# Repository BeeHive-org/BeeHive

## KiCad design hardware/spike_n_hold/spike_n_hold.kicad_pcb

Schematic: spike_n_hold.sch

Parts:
C1, C2: 680pF; C_Disc_D5.1mm_W3.2mm_P5.00mm
C3, C4, C7, C8: 10nF; C_Disc_D5.1mm_W3.2mm_P5.00mm
C5, C6: 10µF; C_Disc_D5.1mm_W3.2mm_P5.00mm
C15: 22µF; CP_Radial_D5.0mm_P2.00mm
D1, D2, D3, D4, D5, D6: 1N4005; D_DO-41_SOD81_P10.16mm_Horizontal
D7, D8: 1N47xxA; D_DO-41_SOD81_P10.16mm_Horizontal
D17: 1N5822; D_DO-201AD_P15.24mm_Horizontal
H1, H2, H3, H4: MountingHole; MountingHole_3.2mm_M3
J1: Conn_01x04_Female; JST_XH_B4B-XH-A_1x04_P2.50mm_Vertical
J3: to_solenoid_2; PinHeader_1x02_P2.54mm_Vertical
J4: to_solenoid_1; PinHeader_1x02_P2.54mm_Vertical
J5, J6, J7: Conn_01x02; JST_XH_B2B-XH-A_1x02_P2.50mm_Vertical
L1: 33µH; L_Radial_D10.0mm_P5.00mm_Neosid_SD12_style3
Q1, Q2: MJH11021G; TO-247-3_Vertical
Q3, Q4, Q5, Q6: MPSA42; TO-92L_Inline_Wide; MPN MPSA42; Digi-Key_PN MPSA42FS-ND
Q7, Q8: MJH11022G; TO-247-3_Vertical
Q9: IRFZ24NPBF; TO-220-3_Vertical
R1, R2, R9, R10: 10k; R_Axial_DIN0411_L9.9mm_D3.6mm_P12.70mm_Horizontal
R3, R4: 4.7k; R_Axial_DIN0411_L9.9mm_D3.6mm_P12.70mm_Horizontal
R5, R6, R7, R8, R11, R12, R15, R16, R17: 330; R_Axial_DIN0411_L9.9mm_D3.6mm_P12.70mm_Horizontal
R13, R14: 2k; R_Axial_DIN0411_L9.9mm_D3.6mm_P12.70mm_Horizontal
R18: 1k; R_Axial_DIN0411_L9.9mm_D3.6mm_P12.70mm_Horizontal
U1, U2, U3: LM555xM; DIP-8_W7.62mm_LongPads

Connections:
+12V: D1.2 (A), D2.2 (A), J5.1, J6.1, L1.1, R9.2, R10.2, R13.2, R14.2, R15.1, U1.4 (R), U1.8 (VCC), U2.4 (R), U2.8 (VCC), U3.4 (R), U3.8 (VCC)
+24V: C15.1, D17.1 (K), J7.1, Q1.3 (E), Q2.3 (E), R1.1, R2.1
GND: C3.1, C4.1, C5.2, C6.2, C7.1, C8.1, C15.2, D3.2 (A), D4.2 (A), J1.4, J5.2, J6.2, J7.2, Q3.1 (E), Q4.1 (E), Q5.1 (E), Q6.1 (E), Q7.3 (E), Q8.3 (E), Q9.3 (S), R18.2, U1.1 (GND), U2.1 (GND), U3.1 (GND)
unnamed: C1.1, R5.2
unnamed: C2.1, R6.2
unnamed: C3.2, U1.5 (CV)
unnamed: C4.2, U2.5 (CV)
unnamed: C5.1, R13.1, U1.6 (THR), U1.7 (DIS)
unnamed: C6.1, R14.1, U2.6 (THR), U2.7 (DIS)
unnamed: C7.2, R16.1, U3.2 (TR), U3.6 (THR)
unnamed: C8.2, U3.5 (CV)
unnamed: D1.1 (K), D5.1 (K), J3.1, Q1.2 (C)
unnamed: D2.1 (K), D6.1 (K), J4.1, Q2.2 (C)
unnamed: D3.1 (K), Q3.2 (B), R5.1
unnamed: D4.1 (K), Q4.2 (B), R6.1
unnamed: D5.2 (A), D7.2 (A)
unnamed: D6.2 (A), D8.2 (A)
unnamed: D7.1 (K), J3.2, Q7.2 (C)
unnamed: D8.1 (K), J4.2, Q8.2 (C)
unnamed: D17.2 (A), L1.2, Q9.2 (D)
unnamed: Q1.1 (B), R3.2
unnamed: Q2.1 (B), R4.2
unnamed: Q3.3 (C), R9.1, U1.2 (TR)
unnamed: Q4.3 (C), R10.1, U2.2 (TR)
unnamed: Q5.2 (B), R7.1
unnamed: Q5.3 (C), R1.2, R3.1
unnamed: Q6.2 (B), R8.1
unnamed: Q6.3 (C), R2.2, R4.1
unnamed: Q7.1 (B), R11.1
unnamed: Q8.1 (B), R12.1
unnamed: Q9.1 (G), R17.2, R18.1
unnamed: R15.2, R16.2, U3.7 (DIS)
unnamed: R17.1, U3.3 (Q)
input_trigger1: C2.2, J1.1, R12.2
input_trigger2: C1.2, J1.2, R11.2
timed_trigger1: R8.2, U2.3 (Q)
timed_trigger2: R7.2, U1.3 (Q)

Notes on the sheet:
C6 and R14 values should/can be changed to increase/decrease the duration of the spike period
C5 and R13 values should/can be changed to increase/decrease the duration of the spike period
LM555's pin 3 frequency depends on pin 7 and 6 resistors values and pin 2 capacitor value, provided pin 5 capacitor remains constant. This configuration provides about 100kHz frequency. It can also be achieved with another set of components. The choice of components depends solely on what is more c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
***

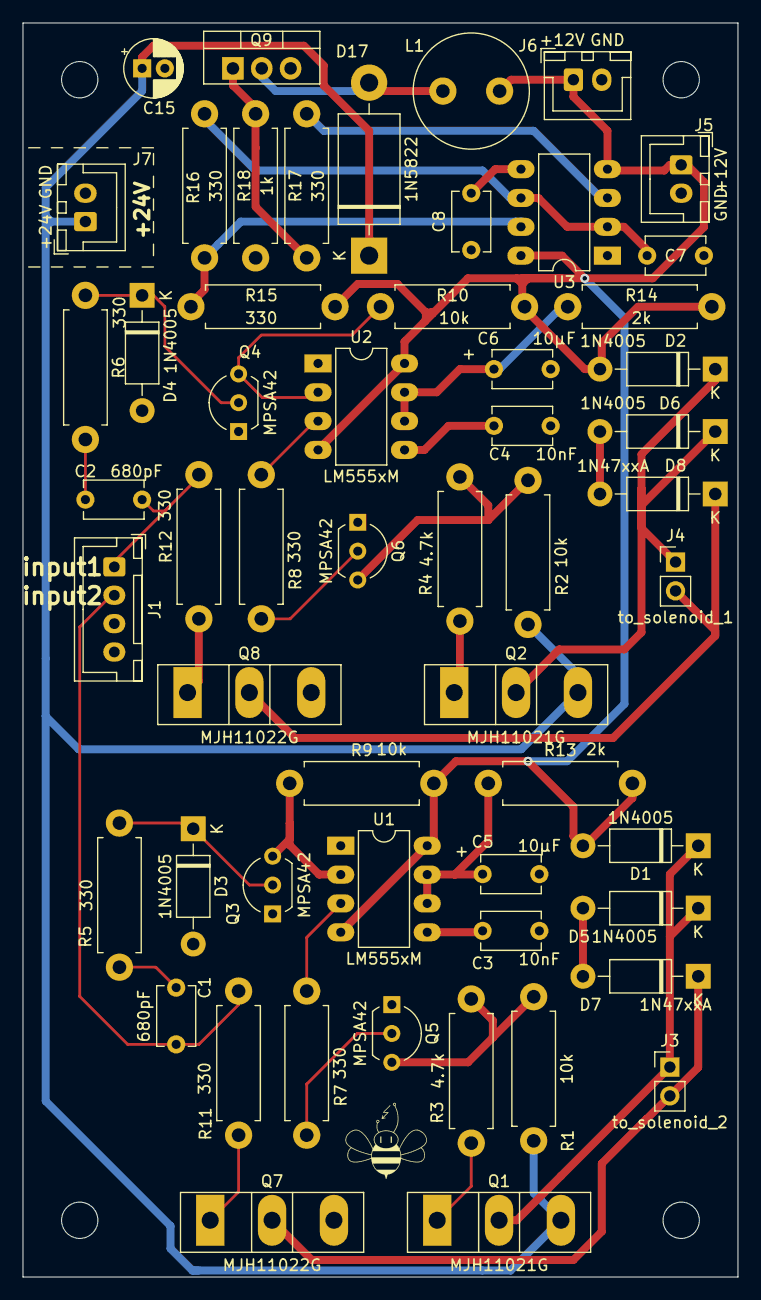
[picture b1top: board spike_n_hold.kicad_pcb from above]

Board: 2 copper layers, 63.0 x 110.5 mm, 59 parts (0 on the bottom side), 37 nets.

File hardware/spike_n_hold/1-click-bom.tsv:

References	Qty	Description	Manufacturer	MPN	Manufacturer	MPN	Manufacturer	MPN	Manufacturer	MPN	Digikey	Mouser	RS	Newark	Farnell
C1, C2	2	C Small 680pF Unpolarized capacitor, small symbol Disc D5.1mm W3.2mm P5.00mm	Vishay 	K681K10X7RF5UH5							BC2690CT-ND   				
C3, C4	2	C Small 10nF Unpolarized capacitor, small symbol Disc D5.1mm W3.2mm P5.00mm	TDK corporation	FA18C0G2A103JRU06							445-175393-1-ND 				
C5, C6	2	C Small 10µF Unpolarized capacitor, small symbol Disc D5.1mm W3.2mm P5.00mm	AVX	TAP106M035SCS							478-6062-ND 				
C11	1	CP Small 680µF Polarized capacitor, small symbol Radial D10.0mm P5.00mm	Rubycon	35PX680MEFC10X16							1189-1282-ND 				
C15	1	CP Small 220µF Polarized capacitor, small symbol Radial D10.0mm P5.00mm	Panasonic	EEU-FM1V221							P12411-ND 				
D1, D5, D3, D2, D6, D4	6	1N4005 50V 1A General Purpose Rectifier Diode, DO-41 D SOD81 P10.16mm Horizontal	micro commercial	1N4005-TP							1N4005-TPMSCT-ND 				
D7, D8	2	1N47xxA 1300mW Zener Diode, DO-41 D SOD81 P10.16mm Horizontal	Vishay 	1N4757A-TR							1N4757AVSCT-ND 				
D17	1	1N5820 20V 3A Schottky Barrier Rectifier Diode, DO-201AD D P15.24mm Horizontal	SMC	SB5100TA							1655-1524-1-ND 				
H4, H3, H1, H2	4	MountingHole Mounting Hole without connection 3.2mm M3													
J1, J2	2	Conn 01x02 Female single row, 01x02 P2.54mm Vertical	Sullins	PPTC101LFBN-RC							S7008-ND 				
J3, J4	2	Screw Terminal 01x02 P2.54mm Vertical													
J9	1	Barrel Jack MountingPin DC with a mounting pin 5.5mmODx2.1mmID PJ-202A	CUI devices	PJ-202AH							CP-202AH-ND				
L1	1	L 33µH Inductor Radial D7.5mm P3.50mm Fastron 07P	Wuerth	7447471330							732-3415-ND 				
Q1, Q2	2	Q PNP Darlington BCE MJH11021G transistor, base/collector/emitter TO-247-3 Vertical	ON semiconductors	MJH11021G							MJH11021GOS-ND 				
Q5, Q6, Q3, Q4	4	MPSA42 TRANS NPN 300V 0.5A TO-92 TO-92L Inline Wide	ON semiconductors	MPSA42	ON semiconductor	KSP42BU 					KSP42BU-ND				
Q7, Q8	2	Q NPN Darlington BCE MJH11022G transistor, base/collector/emitter TO-247-3 Vertical	ON semiconductors	MJH11022G							MJH11022GOS-ND 				
R1, R9, R2, R10	4	R Small 10k Resistor, small symbol Axial DIN0411 L9.9mm D3.6mm P12.70mm Horizontal	Stackpole	CF14JT10K0							CF14JT10K0CT-ND 				
R3, R4	2	R Small 4.7k Resistor, small symbol Axial DIN0411 L9.9mm D3.6mm P12.70mm Horizontal	Stackpole	CF14JT4K70							CF14JT4K70CT-ND 				
R7, R11, R5, R8, R12, R6	6	R Small 330 Resistor, small symbol Axial DIN0411 L9.9mm D3.6mm P12.70mm Horizontal	Stackpole	CF14JT330R							CF14JT330RCT-ND 				
R13, R14	2	R Small 2k Resistor, small symbol Axial DIN0411 L9.9mm D3.6mm P12.70mm Horizontal	Stackpole	CF14JT2K00							CF14JT2K00CT-ND				
R15	1	R Small 1k Resistor, small symbol Axial DIN0411 L9.9mm D3.6mm P12.70mm Horizontal	Stackpole	CF14JT1K00							CF14JT1K00CT-ND				
R16	1	R Small 9.1k Resistor, small symbol Axial DIN0411 L9.9mm D3.6mm P12.70mm Horizontal	Stackpole	RNMF14FAD9K10							RNMF14FAD9K10CT-ND				
U1, U2	2	LM555xM Precision Timers, 555 compatible, SOIC-8 DIP-8 W7.62mm LongPads	Texas instruments	NA555P 							296-21753-5-ND 				
U5	1	LM2596T-ADJ 12V 3A 150kHz Step-Down Voltage Regulator, TO-220 TO-220-5 	Texas instruments	LM2596T-ADJ/LF02 							296-49677-ND

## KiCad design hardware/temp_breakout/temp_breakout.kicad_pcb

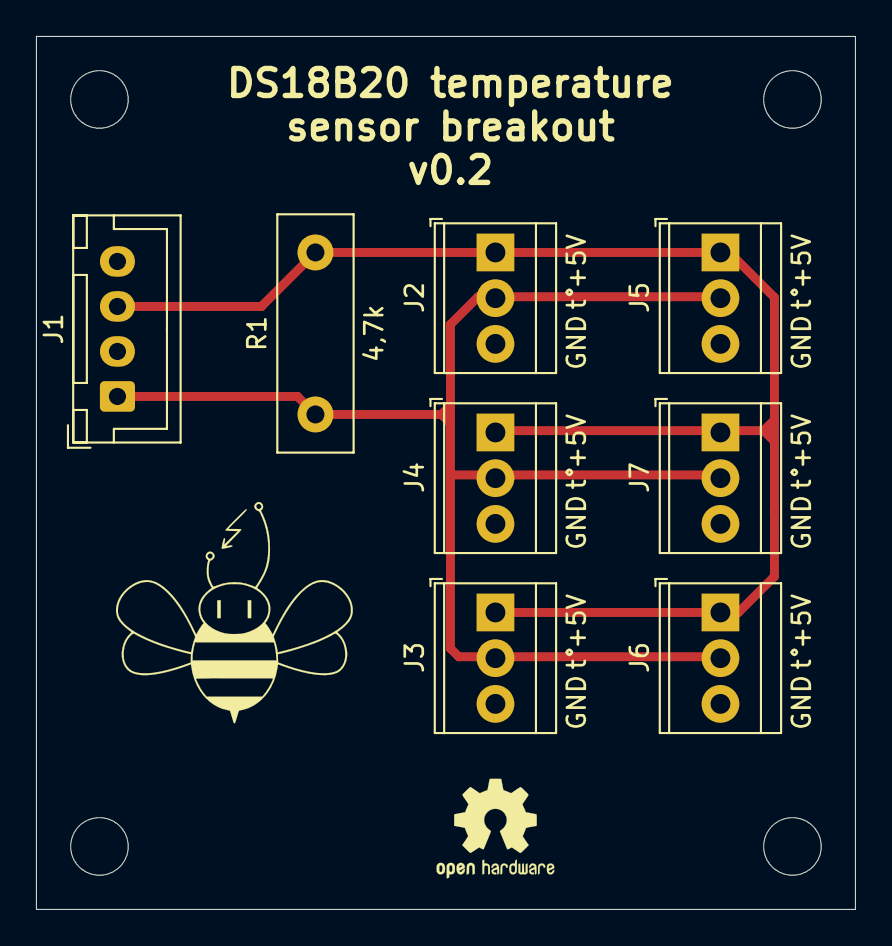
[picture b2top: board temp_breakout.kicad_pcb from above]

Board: 2 copper layers, 45.5 x 48.5 mm, 8 parts (0 on the bottom side), 3 nets.

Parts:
J1: Conn_01x04; JST_XH_B4B-XH-A_1x04_P2.50mm_Vertical
J2, J3, J4, J5, J6, J7: Conn_01x03; TerminalBlock_TE_282834-3_1x03_P2.54mm_Horizontal
R1: 4,7k; R_Box_L13.0mm_W4.0mm_P9.00mm

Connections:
+5V: J1.3, J2.1, J3.1, J4.1, J5.1, J6.1, J7.1, R1.2
GND: J1.4, J2.3, J3.3, J4.3, J5.3, J6.3, J7.3
esp_pin: J1.1, J2.2, J3.2, J4.2, J5.2, J6.2, J7.2, R1.1

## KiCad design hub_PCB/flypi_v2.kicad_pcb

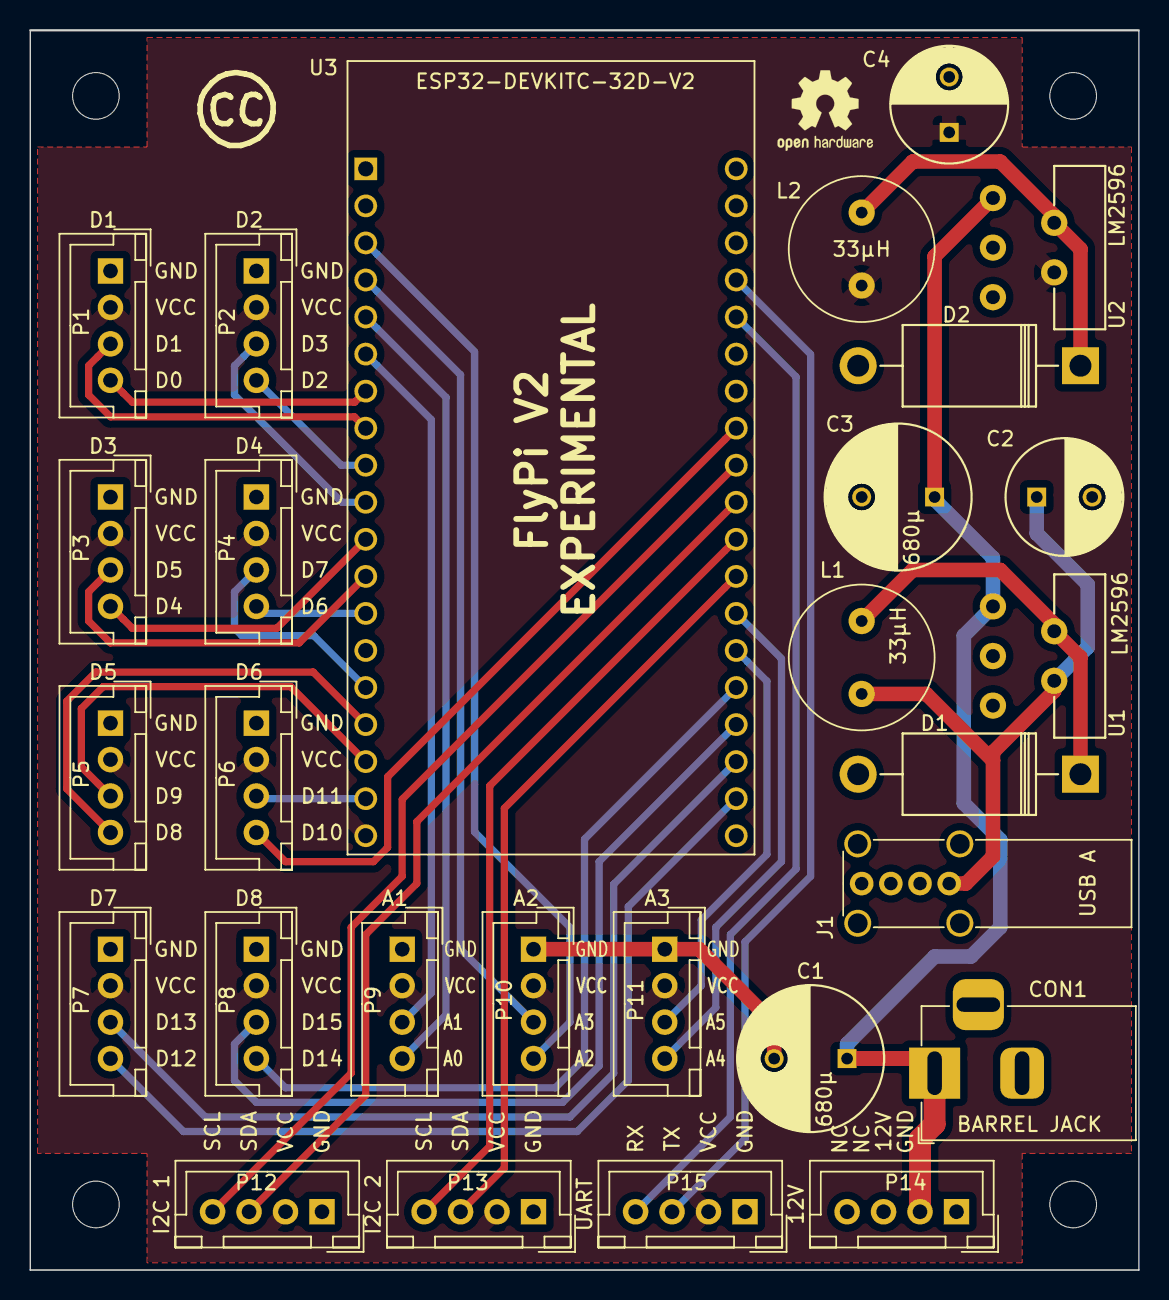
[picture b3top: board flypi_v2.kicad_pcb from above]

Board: 2 copper layers, 76.0 x 85.0 mm, 30 parts (0 on the bottom side), 34 nets.

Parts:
 : OSHW-Logo2_7.3x6mm_SilkScreen
 #2: Symbol_CreativeCommons_SilkScreenTop_Type2_Small
C1, C3: 680µ; C_Radial_D10_L21_P5
C2, C4: 220µ; C_Radial_D8_L13_P3.8
CON1: BARREL JACK; BarrelJack_Horizontal
D1, D2: Schottky 5A; Diode_DO-201AD_Horizontal_RM15
J1: USB A; USB_A_Vertical
L1, L2: 33µH; Neosid_Inductor_MA-Bs75
P1: D1; JST_XH_B04B-XH-A_04x2.50mm_Straight
P2: D2; JST_XH_B04B-XH-A_04x2.50mm_Straight
P3: D3; JST_XH_B04B-XH-A_04x2.50mm_Straight
P4: D4; JST_XH_B04B-XH-A_04x2.50mm_Straight
P5: D5; JST_XH_B04B-XH-A_04x2.50mm_Straight
P6: D6; JST_XH_B04B-XH-A_04x2.50mm_Straight
P7: D7; JST_XH_B04B-XH-A_04x2.50mm_Straight
P8: D8; JST_XH_B04B-XH-A_04x2.50mm_Straight
P9: A1; JST_XH_B04B-XH-A_04x2.50mm_Straight
P10: A2; JST_XH_B04B-XH-A_04x2.50mm_Straight
P11: A3; JST_XH_B04B-XH-A_04x2.50mm_Straight
P12: I2C 1; JST_XH_B04B-XH-A_04x2.50mm_Straight
P13: I2C 2; JST_XH_B04B-XH-A_04x2.50mm_Straight
P14: 12V; JST_XH_B04B-XH-A_04x2.50mm_Straight
P15: UART; JST_XH_B04B-XH-A_04x2.50mm_Straight
U1, U2: LM2596
U3: ESP32-DEVKITC-32D-V2; MODULE_ESP32-DEVKITC-32D

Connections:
+5V: C4.1, L2.2, P1.2, P2.2, P3.2, P4.2, P5.2, P6.2, P7.2, P8.2, P9.2, P10.2, P11.2, P12.2, P13.2, P15.2, U2.4, U3.19
A1-3: P9.3, U3.6
A1-4: P9.4, U3.5
A2-3: P10.3, U3.4
A2-4: P10.4, U3.3
A3-3: P11.3, U3.33
A3-4: P11.4, U3.32
D1-3: P1.3, U3.8
D1-4: P1.4, U3.7
D2-3: P2.3, U3.10
D2-4: P2.4, U3.9
D3-3: P3.3, U3.12
D3-4: P3.4, U3.11
D4-3: P4.3, U3.15
D4-4: P4.4, U3.13
D5-3: P5.3, U3.17
D5-4: P5.4, U3.16
D6-3: P6.3, U3.18
D6-4: P6.4, U3.27
D7-3: P7.3, U3.36
D7-4: P7.4, U3.37
D8-3: P8.3, U3.35
D8-4: P8.4, U3.34
GND: C1.2, C2.2, C3.2, C4.2, CON1.2, CON1.3, D1.2, D2.2, J1.4, J1.5, P1.1, P2.1, P3.1, P4.1, P5.1, P6.1, P7.1, P8.1, P9.1, P10.1, P11.1, P12.1, P13.1, P14.1, P15.1, U1.3, U1.5, U2.3, U2.5, U3.14, U3.20, U3.26
I2C_1-3: P12.3, U3.29
I2C_1-4: P12.4, U3.28
I2C_2-3: P13.3, U3.31
I2C_2-4: P13.4, U3.30
unnamed: C1.1, C3.1, CON1.1, P14.2, U1.1, U2.1
unnamed: C2.1, J1.1, L1.2, U1.4
unnamed: D1.1, L1.1, U1.2
unnamed: D2.1, L2.1, U2.2
RX: P15.4, U3.24
TX: P15.3, U3.23

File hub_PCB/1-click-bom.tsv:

References	Qty	Description	Manufacturer	MPN	Manufacturer_1	MPN_2	Manufacturer_3	MPN_4	Manufacturer_5	MPN_6	Manufacturer_7	MPN_8	Digikey	Mouser	RS	Newark	Farnell
U1	 U2	2	LM2596 5v	ITO-220	Texas Instruments	Texas Instruments	LM2596T-5.0/NOPB							LM2596T-5.0/NOPB-ND	926LM2596T5.0/NOPB	5333743	97K3256	1150103
U3	1	ESP32-DevKitC-VIB 
P1	P2	P3	P4	P5	P6	P7	P8	P9	P10	P11	P12	P13	P14	P15	15	CONN HEADER XH TOP 4POS 2.5MM	JST	B4B-XH-A (LF)(SN) 									455-2249-ND 		820-1551		1516278
L1	 L2	2	INDUCTOR 33µH Neosid MA-Bs75	Bourns	RLB0914-330KL									RLB0914-330KL-ND	652RLB0914330KL	8118853	61J7916	2309242
J1	1	USB A Vertical	FCI	73725-0110BLF	Molex	48204-0001							609-1041-ND	649737250110BLF	7710048	56R0832	2782046
D1, D2	2	Diode Schottky 5A DO-201AD	Vishay	1N5822-E3/73	Zetex	SB5100-T							1N5822-E3/73GICT-ND	6251N5822E3/73	751-4843	17T8202	1336553
CON1;	1	2.1mm socket	Cliff	FC68148 DC10A	Lumberg	NEB 21 R	Cliff	FC68148	Gravitech	CON-SOCJ-2155	Parallax	452-00007	452-00007-ND	992CONSOCJ2155	5051609	08WX2563	224959
C1, C3	2	680µF Capacitor	Rubycon	16ZL680MEFC10X16	Panasonic	EEU-FC1A681	Panasonic	EEU-FP1E681 					1189-3978-ND	667-EEU-FP1E681 	7037258	31M6417	1144691
C2, C4	2	CAP ALUM 220UF 20% 25V RADIAL	Panasonic	 EEU-FM1E221 	Panasonic	ECA-1CM221B	Panasonic	ECE-A0GKS221	Panasonic	EEU-EB1A221S			P12383-ND	667ECA1CM221B	7472036	70K9673	9451099

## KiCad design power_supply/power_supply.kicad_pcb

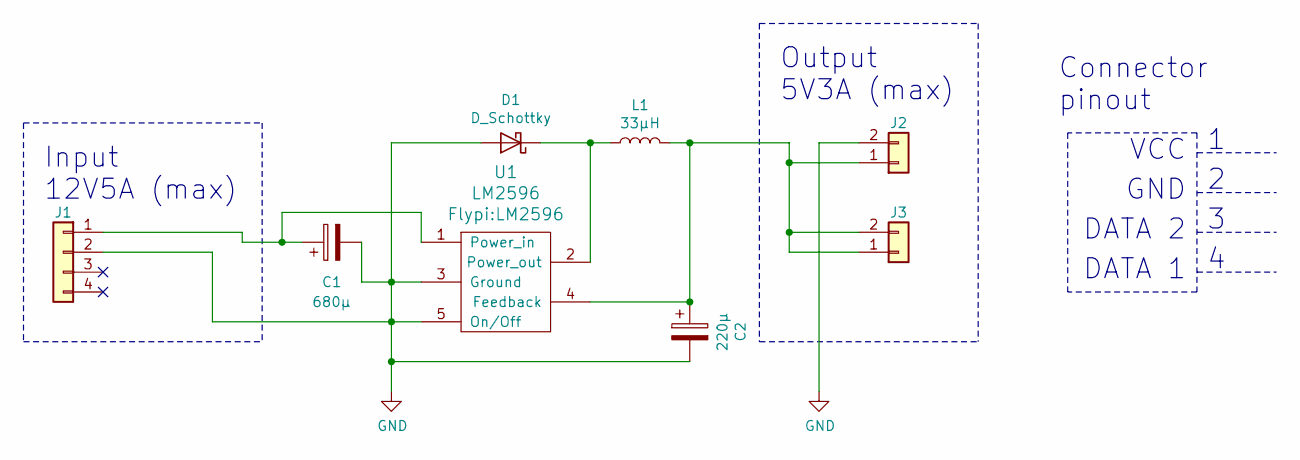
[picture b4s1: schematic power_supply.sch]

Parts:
C1: 680µ; CP_Radial_D10.0mm_P5.00mm
C2: 220µ; CP_Radial_D8.0mm_P3.80mm
D1: D_Schottky; D_DO-201_P15.24mm_Horizontal
J1: Conn_01x04; JST_XH_B4B-XH-A_1x04_P2.50mm_Vertical
J2, J3: Conn_01x02; JST_XH_B2B-XH-A_1x02_P2.50mm_Vertical
L1: 33µH; L_Radial_D10.0mm_P5.00mm_Neosid_SD12_style3
U1: LM2596

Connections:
GND: C1.2, C2.2, D1.2 (A), J1.2, J2.2, U1.3 (Ground), U1.5 (On/Off)
unnamed: C1.1, J1.1, U1.1 (Power_in)
unnamed: C2.1, J2.1, J3.1, J3.2, L1.2, U1.4 (Feedback)
unnamed: D1.1 (K), L1.1, U1.2 (Power_out)

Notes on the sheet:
GND
VCC
DATA 2
DATA 1
Connector pinout
Input 12V5A (max)
Output 5V3A (max)

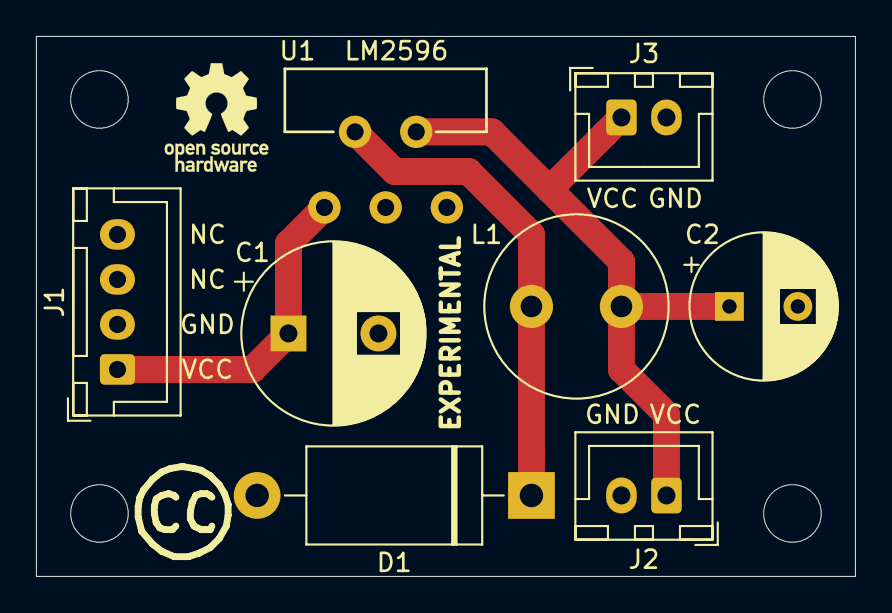
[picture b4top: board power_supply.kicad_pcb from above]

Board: 2 copper layers, 45.5 x 30.0 mm, 8 parts (0 on the bottom side), 4 nets.

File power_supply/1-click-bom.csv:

References,Qty,Description,Manufacturer,MPN,Manufacturer_1,MPN_2,Manufacturer_3,MPN_4,Manufacturer_5,MPN_6,Manufacturer_7,MPN_8,Digikey,Mouser,RS,Newark,Farnell
U1;,2,LM2596 5v,ITO-220,Texas Instruments,Texas Instruments,LM2596T-5.0/NOPB,,,,,,,LM2596T-5.0/NOPB-ND,926LM2596T5.0/NOPB,5333743,97K3256,1150103
J1;,1,CONN HEADER XH TOP 4POS 2.5MM,JST,B4B-XH-A (LF)(SN) ,,,,,,,,,455-2249-ND ,,820-1551,,1516278
J2; J3;,2,CONN HEADER XH TOP 2POS 2.5MM,JST,B2B-XH-A (LF)(SN),,,,,,,,,455-2247-ND,,8201554P,73M9415,1516276
L1; ,1,INDUCTOR 33µH Neosid MA-Bs75,Bourns,RLB0914-330KL,,,,,,,,,RLB0914-330KL-ND,652RLB0914330KL,8118853,61J7916,2309242
D1; ,1,Diode Schottky 5A DO-201AD,Vishay,1N5822-E3/73,Zetex,SB5100-T,,,,,,,1N5822-E3/73GICT-ND,6251N5822E3/73,751-4843,17T8202,1336553
C1;,1,680µF Capacitor,Rubycon,16ZL680MEFC10X16,Panasonic,EEU-FC1A681,Panasonic,EEU-FP1E681 ,,,,,1189-3978-ND,667-EEU-FP1E681 ,7037258,31M6417,1144691
C2; ,1,CAP ALUM 220UF 20% 25V RADIAL,Panasonic, EEU-FM1E221 ,Panasonic,ECA-1CM221B,Panasonic,ECE-A0GKS221,Panasonic,EEU-EB1A221S,,,P12383-ND,667ECA1CM221B,7472036,70K9673,9451099

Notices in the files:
hardware/spike_n_hold/spike_n_hold.kicad_pcb:
spike and hold circuit (2X) CERN OHL V2 S 20200202
